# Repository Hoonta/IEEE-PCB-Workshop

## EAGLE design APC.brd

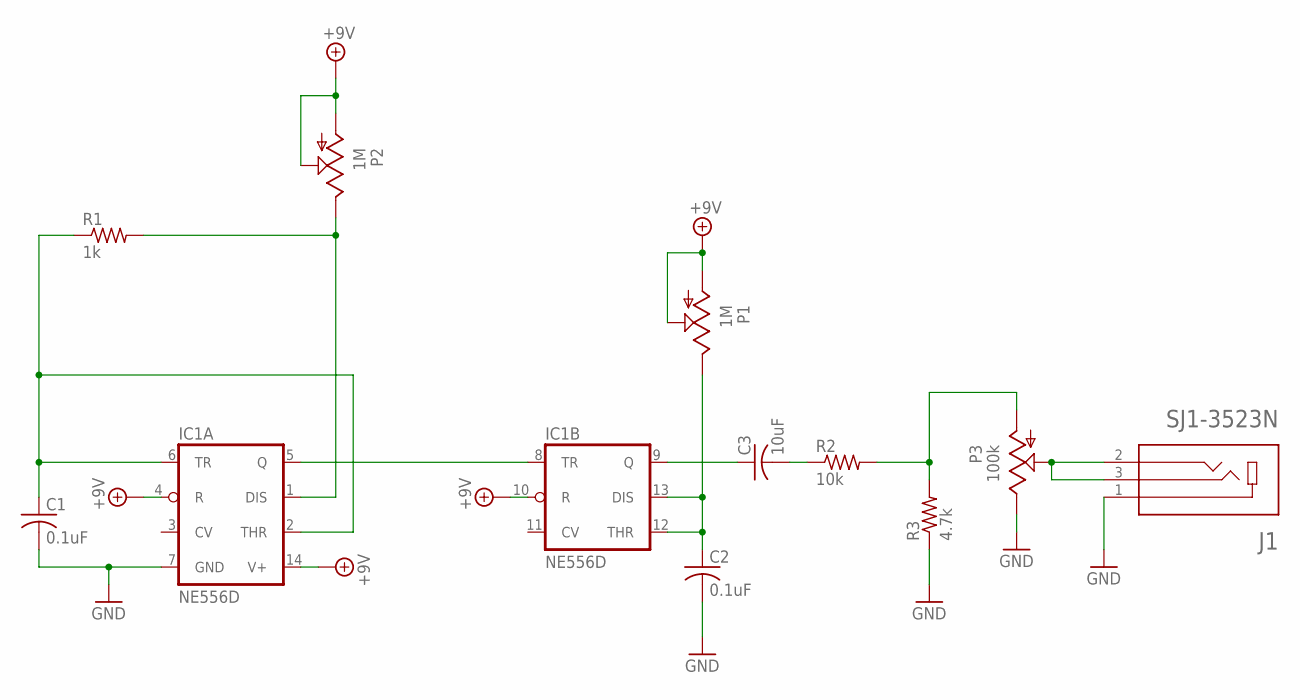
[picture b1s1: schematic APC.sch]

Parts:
C1, C2: 0.1uF; C0805
C3: 10uF; C0805
IC1: NE556D; SO14
J1: SJ1-3523N; CUI_SJ1-3523N
P1, P2: 1M; PT-10
P3: 100k; PT-10
R1: 1k; R0805
R2: 10k; R0805
R3: 4.7k; R0805

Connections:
+9V: IC1.4 (R), IC1.10 (R), IC1.14 (V+), P1.A, P1.S, P2.A, P2.S
GND: C1.2, C2.2, IC1.7 (GND), J1.1, P3.E, R3.1
unnamed: IC1.5 (Q), IC1.8 (TR)
unnamed: C1.1, IC1.2 (THR), IC1.6 (TR), R1.1
unnamed: C2.1, IC1.12 (THR), IC1.13 (DIS), P1.E
unnamed: IC1.1 (DIS), P2.E, R1.2
unnamed: C3.2, R2.1
unnamed: C3.1, IC1.9 (Q)
unnamed: J1.2, J1.3, P3.S
unnamed: P3.A, R2.2, R3.2

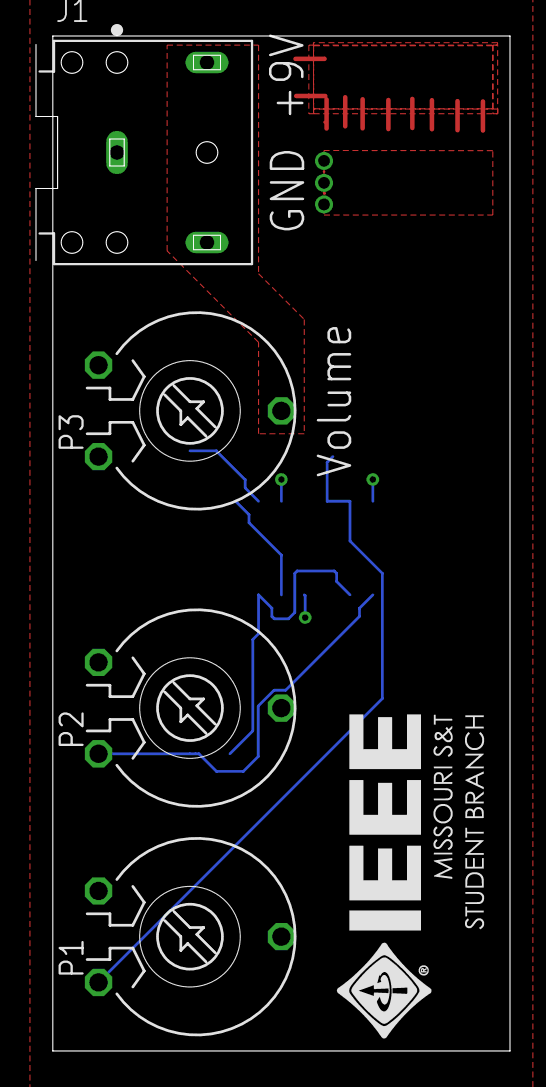
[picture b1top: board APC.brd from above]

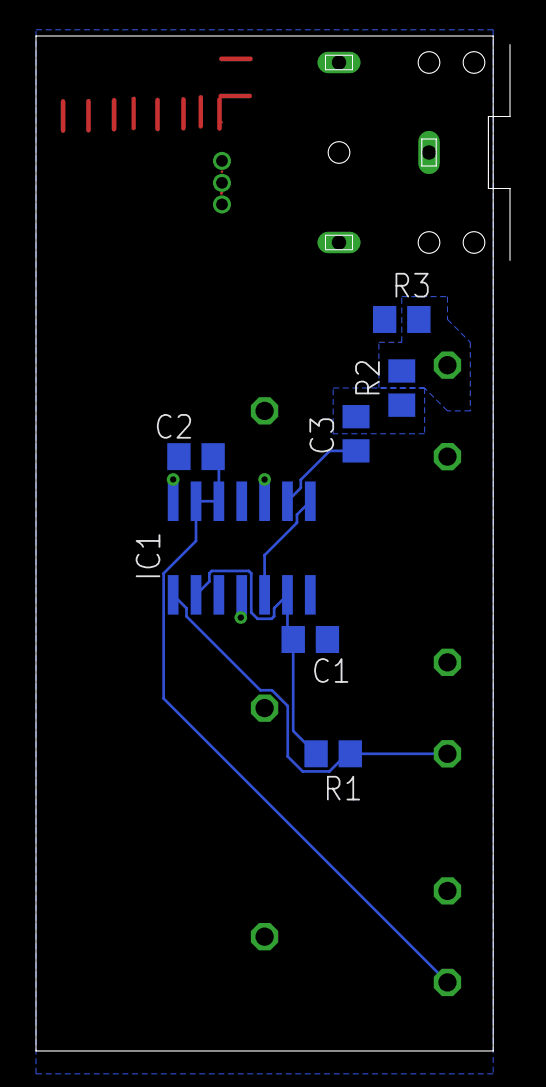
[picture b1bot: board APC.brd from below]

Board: 2 copper layers, 26.3 x 56.4 mm, 11 parts (7 on the bottom side), 10 nets.

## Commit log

2021-03-16 Updated .gitignore
2021-03-16 Created APC.pdf
2021-04-01 V2
    Updated schematic to use all digikey parts. Added solderable pads for power
2021-04-01 JLC Gerber created
    Ready for ordering
